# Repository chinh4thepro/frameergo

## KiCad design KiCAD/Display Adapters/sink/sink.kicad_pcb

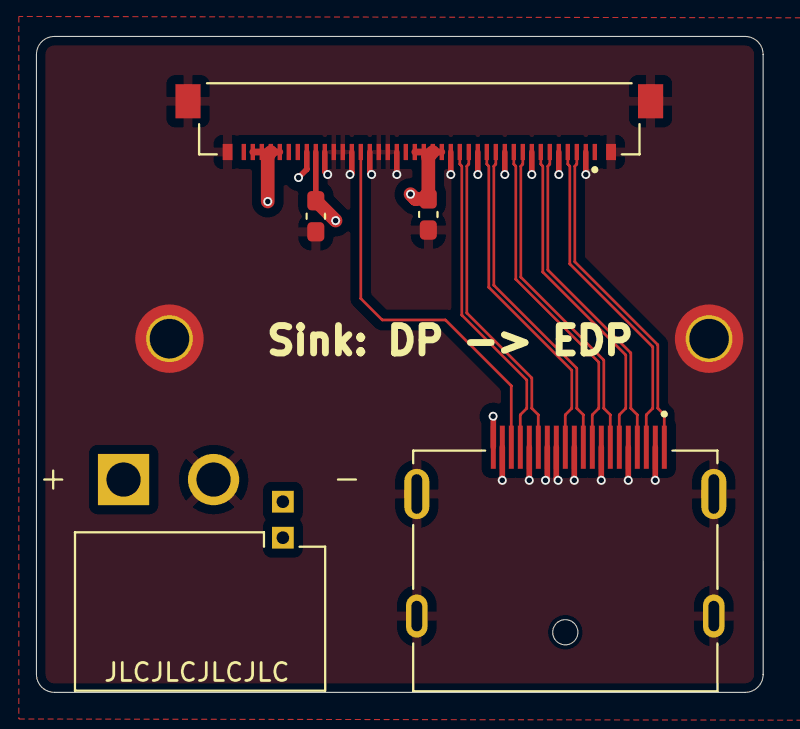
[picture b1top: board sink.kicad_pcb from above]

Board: 4 copper layers, 40.4 x 36.4 mm, 7 parts (0 on the bottom side), 16 nets.

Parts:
C1, C2: 1uF; C_0603_1608Metric_Pad1.08x0.95mm_HandSolder
H1, H2: MountingHole_Pad; MountingHole_2.2mm_M2_DIN965_Pad_TopBottom
J1: 47272-0001; MOLEX_47272-0001
J2: XT30PW_2_2_-M.G.B; AMASS_XT30PW_2_2_-M.G.B
J3: 20455-040E-76; IPEX_20455-040E-76

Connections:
0_EDP_TX_N: J1.10, J3.12
0_EDP_TX_P: J1.12, J3.13
1_EDP_TX_N: J1.7, J3.9
1_EDP_TX_P: J1.9, J3.10
2_EDP_TX_N: J1.4, J3.6
2_EDP_TX_P: J1.6, J3.7
3_EDP_TX_N: J1.1, J3.3
3_EDP_TX_P: J1.3, J3.4
+3.3V: C1.1, J1.20, J3.18, J3.19, J3.20, J3.21
+5V: J2.P, J3.36, J3.37, J3.38, J3.39
AUX_N: J1.17, J3.16
AUX_P: J1.15, J3.15
BLK_OFF_N: C2.2, J2.S1, J3.32
BLK_PWM_LCD: J2.S2, J3.33
EDP_HPD: J1.18, J3.27
GND: C1.2, C2.1, H1.1, H2.1, J1.2, J1.5, J1.8, J1.11, J1.13, J1.14, J1.16, J1.19, J1.S1 (SHIELD), J1.S2 (SHIELD), J1.S3 (SHIELD), J1.S4 (SHIELD), J2.N, J3.2, J3.5, J3.8, J3.11, J3.14, J3.17, J3.23, J3.24, J3.25, J3.26, J3.28, J3.29, J3.30, J3.31, J3.S1 (SHIELD), J3.S2 (SHIELD), J3.S3 (SHIELD), J3.S4 (SHIELD)

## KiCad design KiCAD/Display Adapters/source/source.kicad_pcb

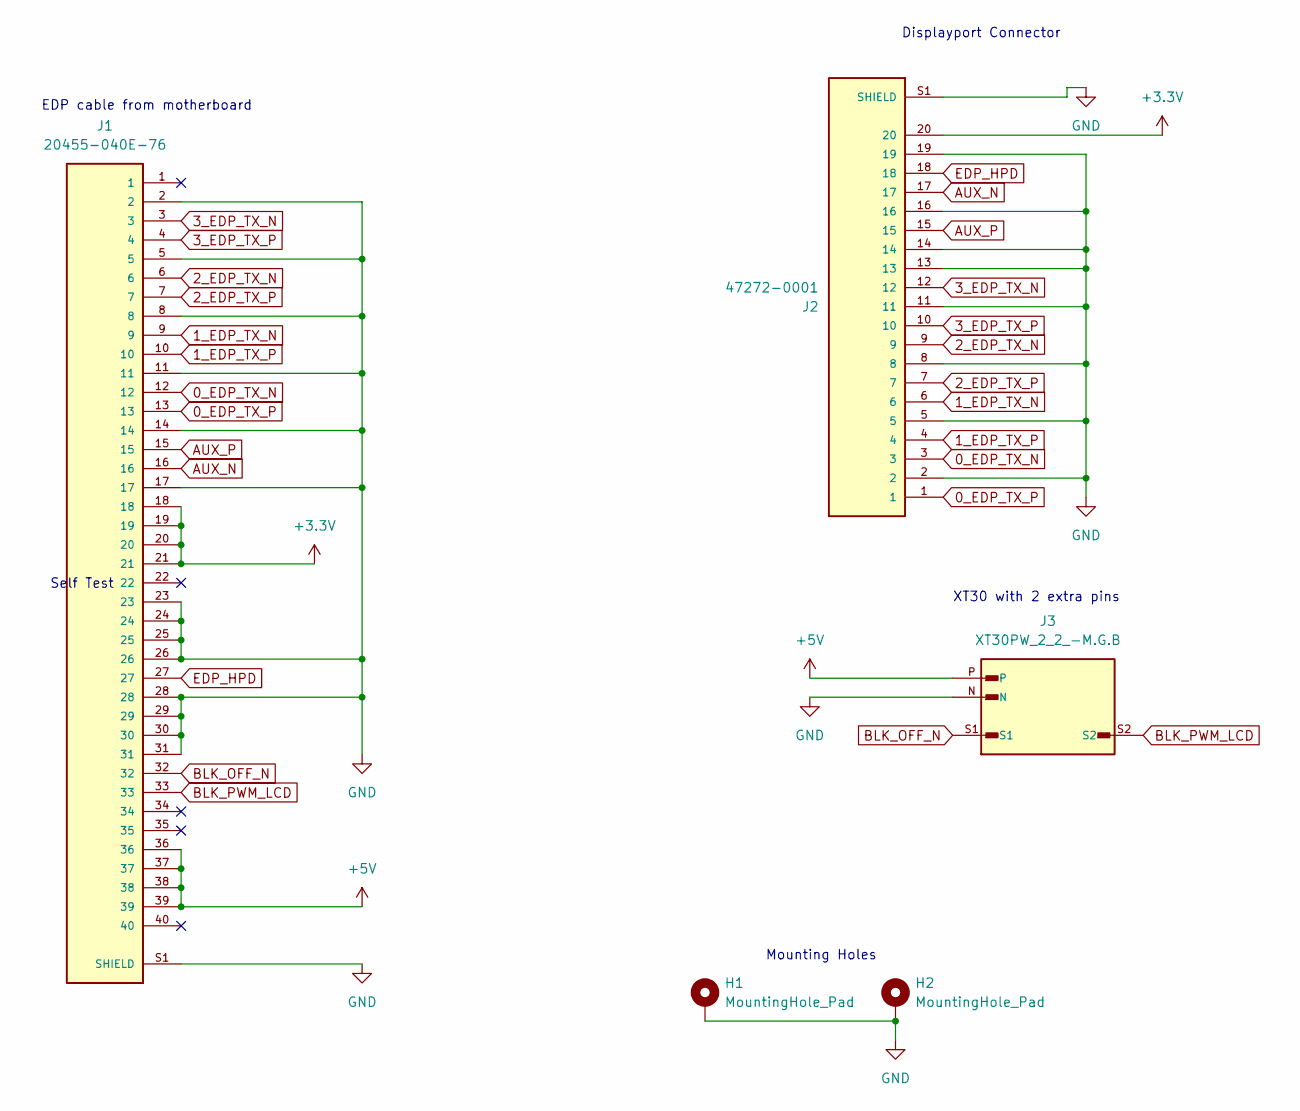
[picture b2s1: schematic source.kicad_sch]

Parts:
H1, H2: MountingHole_Pad; MountingHole_2.2mm_M2_DIN965_Pad_TopBottom
J1: 20455-040E-76; IPEX_20455-040E-76
J2: 47272-0001; MOLEX_47272-0001
J3: XT30PW_2_2_-M.G.B; AMASS_XT30PW_2_2_-M.G.B; PARTREV NA

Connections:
0_EDP_TX_N: J1.12, J2.3
0_EDP_TX_P: J1.13, J2.1
1_EDP_TX_N: J1.9, J2.6
1_EDP_TX_P: J1.10, J2.4
2_EDP_TX_N: J1.6, J2.9
2_EDP_TX_P: J1.7, J2.7
3_EDP_TX_N: J1.3, J2.12
3_EDP_TX_P: J1.4, J2.10
+3.3V: J1.18, J1.19, J1.20, J1.21, J2.20
+5V: J1.36, J1.37, J1.38, J1.39, J3.P
AUX_N: J1.16, J2.17
AUX_P: J1.15, J2.15
BLK_OFF_N: J1.32, J3.S1
BLK_PWM_LCD: J1.33, J3.S2
EDP_HPD: J1.27, J2.18
GND: H1.1, H2.1, J1.2, J1.5, J1.8, J1.11, J1.14, J1.17, J1.23, J1.24, J1.25, J1.26, J1.28, J1.29, J1.30, J1.31, J1.S1 (SHIELD), J1.S2 (SHIELD), J1.S3 (SHIELD), J1.S4 (SHIELD), J2.2, J2.5, J2.8, J2.11, J2.13, J2.14, J2.16, J2.19, J2.S1 (SHIELD), J2.S2 (SHIELD), J2.S3 (SHIELD), J2.S4 (SHIELD), J3.N

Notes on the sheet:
XT30 with 2 extra pins
Mounting Holes
Displayport Connector
EDP cable from motherboard
Self Test

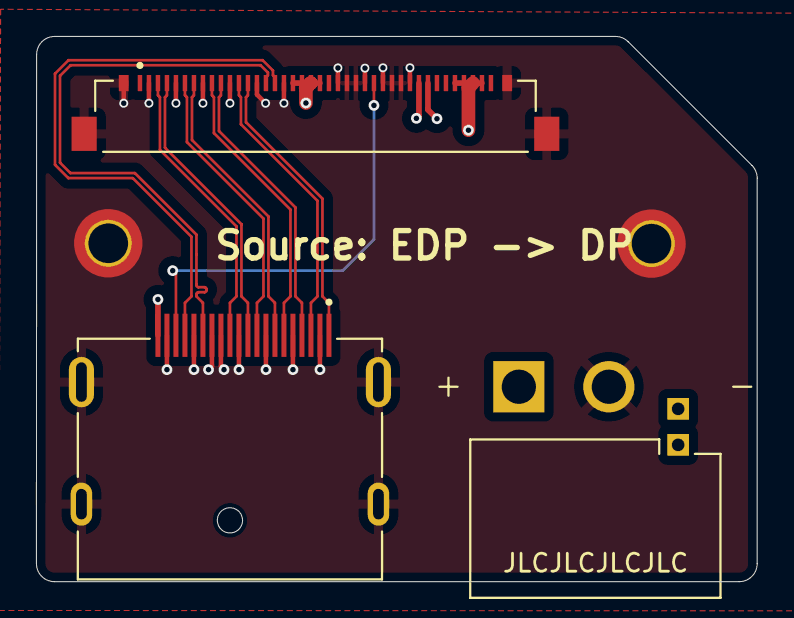
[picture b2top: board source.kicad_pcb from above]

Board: 4 copper layers, 40.0 x 30.3 mm, 5 parts (0 on the bottom side), 16 nets.

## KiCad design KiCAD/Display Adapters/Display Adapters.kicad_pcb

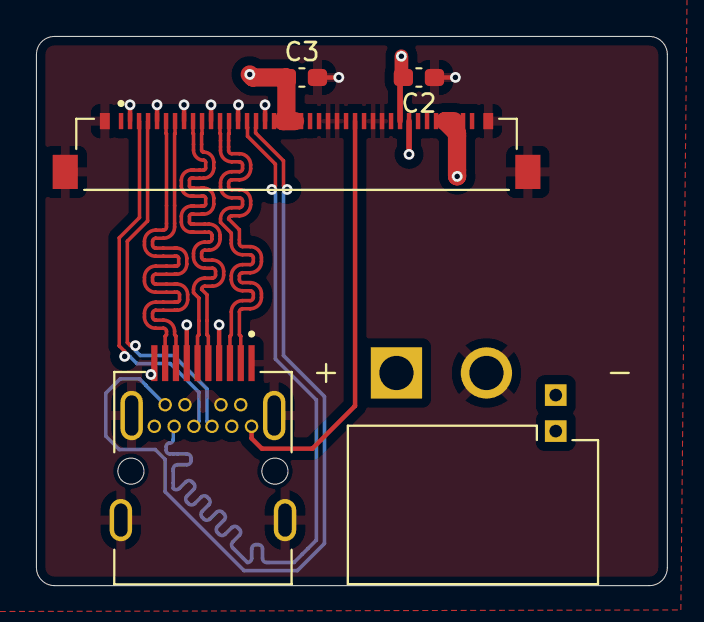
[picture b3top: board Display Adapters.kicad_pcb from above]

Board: 4 copper layers, 35.1 x 30.5 mm, 5 parts (0 on the bottom side), 16 nets.

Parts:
C2, C3: 1uF; C_0603_1608Metric_Pad1.08x0.95mm_HandSolder
J4: XT30PW_2_2_-M.G.B; AMASS_XT30PW_2_2_-M.G.B
J5: G46M2013201AWEU; AMPHENOL_G46M2013201AWEU
J6: 20455-040E-76; IPEX_20455-040E-76

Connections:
0_EDP_TX_N: J5.5 (ML_LANE0_N), J6.12
0_EDP_TX_P: J5.3 (ML_LANE0_P), J6.13
1_EDP_TX_N: J5.11 (ML_LANE1_N), J6.9
1_EDP_TX_P: J5.9 (ML_LANE1_P), J6.10
2_EDP_TX_N: J5.17 (ML_LANE2_N), J6.6
2_EDP_TX_P: J5.15 (ML_LANE2_P), J6.7
3_EDP_TX_N: J5.12 (ML_LANE3_N), J6.3
3_EDP_TX_P: J5.10 (ML_LANE3_P), J6.4
+3.3V: C3.1, J5.4 (CONFIG1), J5.6 (CONFIG2), J5.20 (DP_PWR), J6.18, J6.19, J6.20, J6.21
+5V: J4.P, J6.36, J6.37, J6.38, J6.39
AUX_N: J5.18 (AUX_CH_N), J6.16
AUX_P: J5.16 (AUX_CH_P), J6.15
BLK_OFF_N: C2.2, J4.S2, J6.32
BLK_PWM_LCD: J4.S1, J6.33
EDP_HPD: J5.2 (HOTPLUG_DETECT), J6.27
GND: C2.1, C3.2, J4.N, J5.1 (GND_1), J5.7 (GND_7), J5.8 (GND_8), J5.13 (GND_13), J5.14 (GND_14), J5.19 (GND_19), J5.S1 (SHIELD), J5.S2 (SHIELD), J5.S3 (SHIELD), J5.S4 (SHIELD), J6.2, J6.5, J6.8, J6.11, J6.14, J6.17, J6.23, J6.24, J6.25, J6.26, J6.28, J6.29, J6.30, J6.31, J6.S1 (SHIELD), J6.S2 (SHIELD), J6.S3 (SHIELD), J6.S4 (SHIELD)

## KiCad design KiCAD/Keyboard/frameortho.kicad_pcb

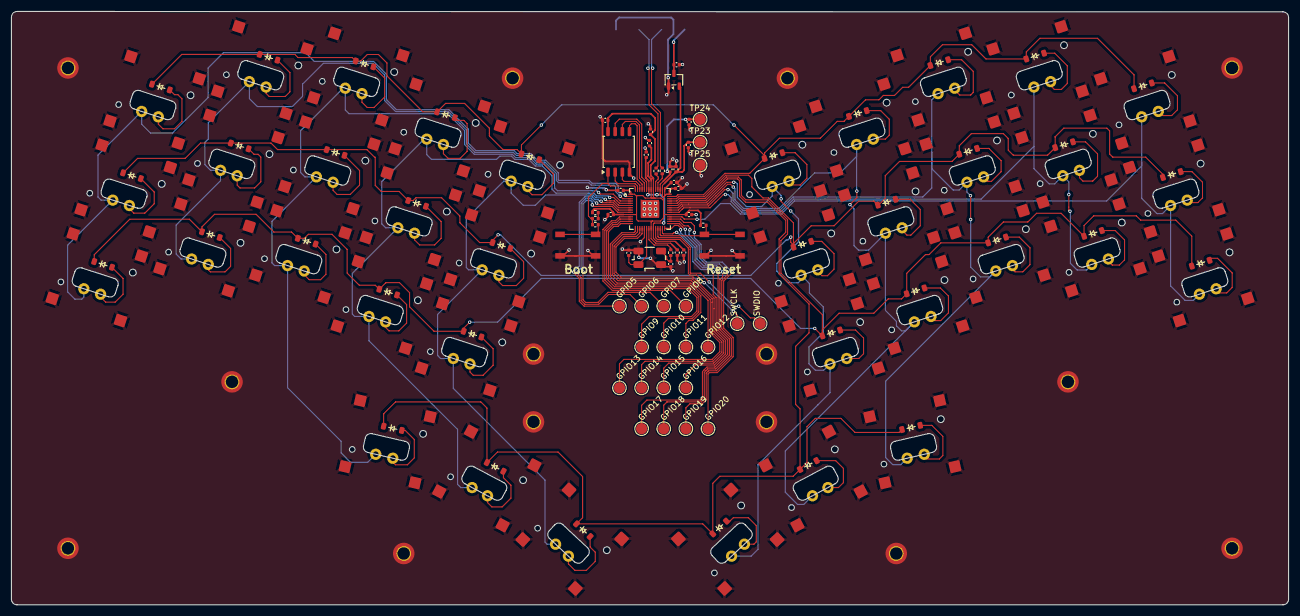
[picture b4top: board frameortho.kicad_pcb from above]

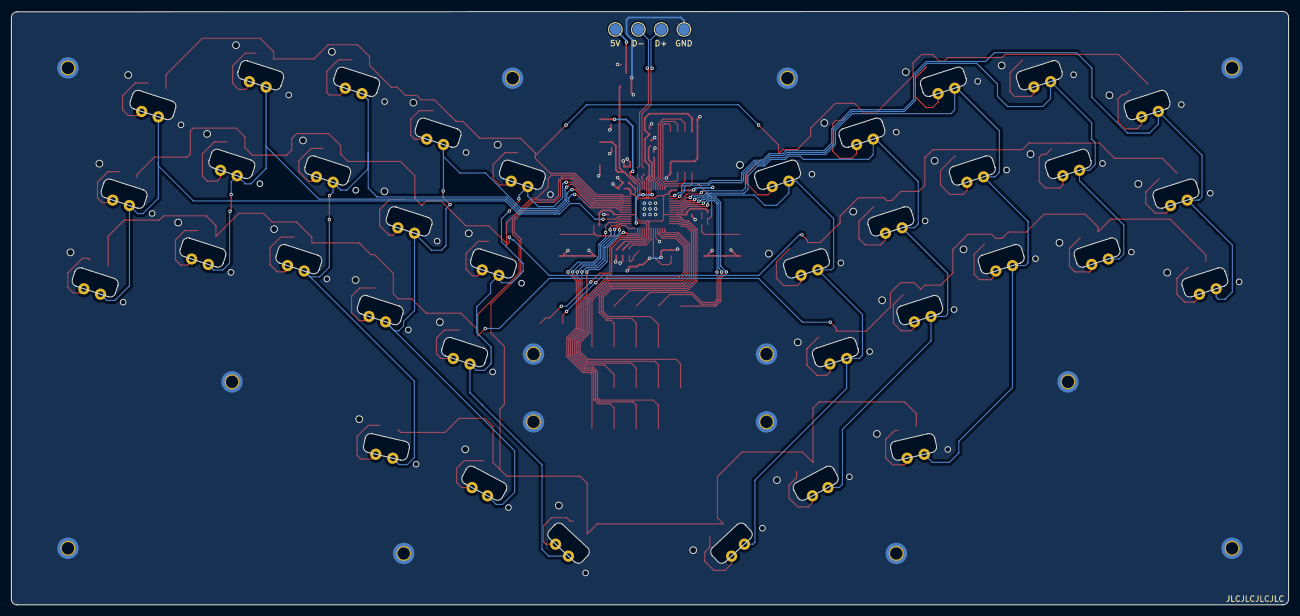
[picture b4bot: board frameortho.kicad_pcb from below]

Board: 2 copper layers, 225.9 x 104.9 mm, 142 parts (4 on the bottom side), 88 nets.

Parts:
C1, C2, C11, C16: 1µF; C_0402_1005Metric
C3, C4, C5, C6, C7, C8, C9, C10, C12, C13, C17, C18: 100nF; C_0402_1005Metric
C14, C15: 27pF; C_0402_1005Metric
D1, D2, D3, D4, D5, D6, D7, D8, D9, D10, D11, D12, D13, D14, D15, D16, D17, D18, D19, D20, D21, D22, D23, D24, D25, D26, D27, D28, D29, D30, D31, D32, D33, D34, D35, D36: D_Small; Diode_SOD-123
H1, H2, H3, H4, H5, H5#2, H6, H7, H8, H9, H10, H11, H12, H13: MountingHole_Pad; MountingHole_2.2mm_M2_DIN965_Pad_TopBottom
R3, R4: 27Ω; R_0402_1005Metric
R5, R7, R8: 5.1kΩ; R_0402_1005Metric
R6, R9: 1kΩ; R_0402_1005Metric
S1, S2, S3, S4, S5, S6, S7, S8, S9, S10, S11, S12, S13, S14, S15, S16, S17, S18, S19, S20, S21, S22, S23, S24, S25, S26, S27, S28, S29, S30, S31, S32, S33, S34, S35, S36: Keyswitch; CPG1316S01D02_castelated_mikecinq
SW1, SW2: SW_Push; Button_TL3342
TP1, TP2, TP3, TP4, TP5, TP6, TP7, TP8, TP9, TP10, TP11, TP12, TP13, TP14, TP15, TP16, TP17, TP18, TP19, TP20, TP21, TP22, TP23, TP24, TP25: TestPoint; TestPoint_Pad_D2.0mm
U1: RP2040; QFN-56-1EP_7x7mm_P0.4mm_EP3.2x3.2mm
U2: W25Q128JVS; SOIC-8_5.3x5.3mm_P1.27mm
U3: XC6206PxxxMR; SOT-23-3
Y1: 12 MHz 18pF; Crystal_SMD_Abracon_ABM3B-4Pin_5.0x3.2mm

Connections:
+1V1: C11.1, C12.1, C13.1, C18.1, TP24.1, U1.23 (DVDD), U1.45 (VREG_VOUT), U1.50 (DVDD)
+3V3: C1.1, C2.1, C3.1, C4.1, C5.1, C6.1, C7.1, C8.1, C9.1, C10.1, C17.1, R5.1, R7.1, TP23.1, U1.1 (IOVDD), U1.10 (IOVDD), U1.22 (IOVDD), U1.33 (IOVDD), U1.42 (IOVDD), U1.43 (ADC_AVDD), U1.44 (VREG_IN), U1.48 (USB_VDD), U1.49 (IOVDD), U2.8 (VCC), U3.2 (VO)
+5V: C16.1, TP17.1, U3.3 (VI)
COL_0: S1.1, S11.1, S21.1, U1.2 (GPIO0)
COL_1: S2.1, S12.1, S22.1, U1.3 (GPIO1)
COL_2: S3.1, S13.1, S23.1, S31.1, U1.4 (GPIO2)
COL_3: S4.1, S14.1, S24.1, S32.1, U1.5 (GPIO3)
COL_4: S5.1, S15.1, S25.1, S33.1, U1.6 (GPIO4)
COL_5: S6.1, S16.1, S26.1, S34.1, U1.37 (GPIO25)
COL_6: S7.1, S17.1, S27.1, S35.1, U1.36 (GPIO24)
COL_7: S8.1, S18.1, S28.1, S36.1, U1.35 (GPIO23)
COL_8: S9.1, S19.1, S29.1, U1.34 (GPIO22)
COL_9: S10.1, S20.1, S30.1, U1.32 (GPIO21)
D_N: R4.2, TP19.1
D_P: R3.2, TP18.1
GND: C1.2, C2.2, C3.2, C4.2, C5.2, C6.2, C7.2, C8.2, C9.2, C10.2, C11.2, C12.2, C13.2, C14.1, C15.1, C16.2, C17.2, C18.2, H1.1, H2.1, H3.1, H4.1, H5.1, H5#2.1, H6.1, H7.1, H8.1, H9.1, H10.1, H11.1, H12.1, H13.1, S1.3, S2.3, S3.3, S4.3, S5.3, S6.3, S7.3, S8.3, S9.3, S10.3, S11.3, S12.3, S13.3, S14.3, S15.3, S16.3, S17.3, S18.3, S19.3, S20.3, S21.3, S22.3, S23.3, S24.3, S25.3, S26.3, S27.3, S28.3, S29.3, S30.3, S31.3, S32.3, S33.3, S34.3, S35.3, S36.3, SW1.1, SW2.1, TP20.1, TP25.1, U1.19 (TESTEN), U1.57 (GND), U2.4 (GND), U3.1 (GND), Y1.2, Y1.4
GPIO5: TP1.1, U1.7 (GPIO5)
GPIO6: TP2.1, U1.8 (GPIO6)
GPIO7: TP3.1, U1.9 (GPIO7)
GPIO8: TP4.1, U1.11 (GPIO8)
GPIO9: TP5.1, U1.12 (GPIO9)
GPIO10: TP6.1, U1.13 (GPIO10)
GPIO11: TP7.1, U1.14 (GPIO11)
GPIO12: TP8.1, U1.15 (GPIO12)
GPIO13: TP9.1, U1.16 (GPIO13)
GPIO14: TP10.1, U1.17 (GPIO14)
GPIO15: TP11.1, U1.18 (GPIO15)
GPIO16: TP12.1, U1.27 (GPIO16)
GPIO17: TP13.1, U1.28 (GPIO17)
GPIO18: TP14.1, U1.29 (GPIO18)
GPIO19: TP15.1, U1.30 (GPIO19)
GPIO20: TP16.1, U1.31 (GPIO20)
unnamed: C15.2, R6.1, Y1.3
unnamed: D1.2 (A), S1.2
unnamed: D2.2 (A), S2.2
unnamed: D3.2 (A), S3.2
unnamed: D4.2 (A), S4.2
unnamed: D5.2 (A), S5.2
unnamed: D6.2 (A), S6.2
unnamed: D7.2 (A), S7.2
unnamed: D8.2 (A), S8.2
unnamed: D9.2 (A), S9.2
unnamed: D10.2 (A), S10.2
unnamed: D11.2 (A), S11.2
unnamed: D12.2 (A), S12.2
unnamed: D13.2 (A), S13.2
unnamed: D14.2 (A), S14.2
unnamed: D15.2 (A), S15.2
unnamed: D16.2 (A), S16.2
unnamed: D17.2 (A), S17.2
unnamed: D18.2 (A), S18.2
unnamed: D19.2 (A), S19.2
unnamed: D20.2 (A), S20.2
unnamed: D21.2 (A), S21.2
unnamed: D22.2 (A), S22.2
unnamed: D23.2 (A), S23.2
unnamed: D24.2 (A), S24.2
unnamed: D25.2 (A), S25.2
unnamed: D26.2 (A), S26.2
unnamed: D27.2 (A), S27.2
unnamed: D28.2 (A), S28.2
unnamed: D29.2 (A), S29.2
unnamed: D30.2 (A), S30.2
unnamed: D31.2 (A), S31.2
unnamed: D32.2 (A), S32.2
unnamed: D33.2 (A), S33.2
unnamed: D34.2 (A), S34.2
unnamed: D35.2 (A), S35.2
unnamed: D36.2 (A), S36.2
unnamed: R5.2, R8.1
unnamed: R9.1, SW2.2
unnamed: R4.1, U1.46 (USB_D_N)
unnamed: R3.1, U1.47 (USB_D_P)
ROW_0: D1.1 (K), D2.1 (K), D3.1 (K), D4.1 (K), D5.1 (K), D6.1 (K), D7.1 (K), D8.1 (K), D9.1 (K), D10.1 (K), U1.41 (GPIO29_ADC3)
ROW_1: D11.1 (K), D12.1 (K), D13.1 (K), D14.1 (K), D15.1 (K), D16.1 (K), D17.1 (K), D18.1 (K), D19.1 (K), D20.1 (K), U1.40 (GPIO28_ADC2)
ROW_2: D21.1 (K), D22.1 (K), D23.1 (K), D24.1 (K), D25.1 (K), D26.1 (K), D27.1 (K), D28.1 (K), D29.1 (K), D30.1 (K), U1.39 (GPIO27_ADC1)
ROW_3: D31.1 (K), D32.1 (K), D33.1 (K), D34.1 (K), D35.1 (K), D36.1 (K), U1.38 (GPIO26_ADC0)
RUN: R7.2, SW1.2, U1.26 (RUN)
SCLK: U1.52 (QSPI_SCLK), U2.6 (CLK)
SD1: U1.55 (QSPI_SD1), U2.2 (DO/IO_{1})
SD2: U1.54 (QSPI_SD2), U2.3 (~WP/IO_{2})
SD3: U1.51 (QSPI_SD3), U2.7 (~HOLD/~RESET/IO_{3})
SDO: U1.53 (QSPI_SD0), U2.5 (DI/IO_{0})
SEL: R8.2, R9.2, U1.56 (QSPI_SS), U2.1 (~CS)
SWCLK: TP21.1, U1.24 (SWCLK)
SWDIO: TP22.1, U1.25 (SWD)
X_IN: C14.2, U1.20 (XIN), Y1.1
X_OUT: R6.2, U1.21 (XOUT)

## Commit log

2025-12-02 source pcb done
2025-12-02 work on sink side
2025-12-03 aaaaaaaaaaaaaaaaaa
2025-12-04 use full sized dp instead
2025-12-05 make board smaller
